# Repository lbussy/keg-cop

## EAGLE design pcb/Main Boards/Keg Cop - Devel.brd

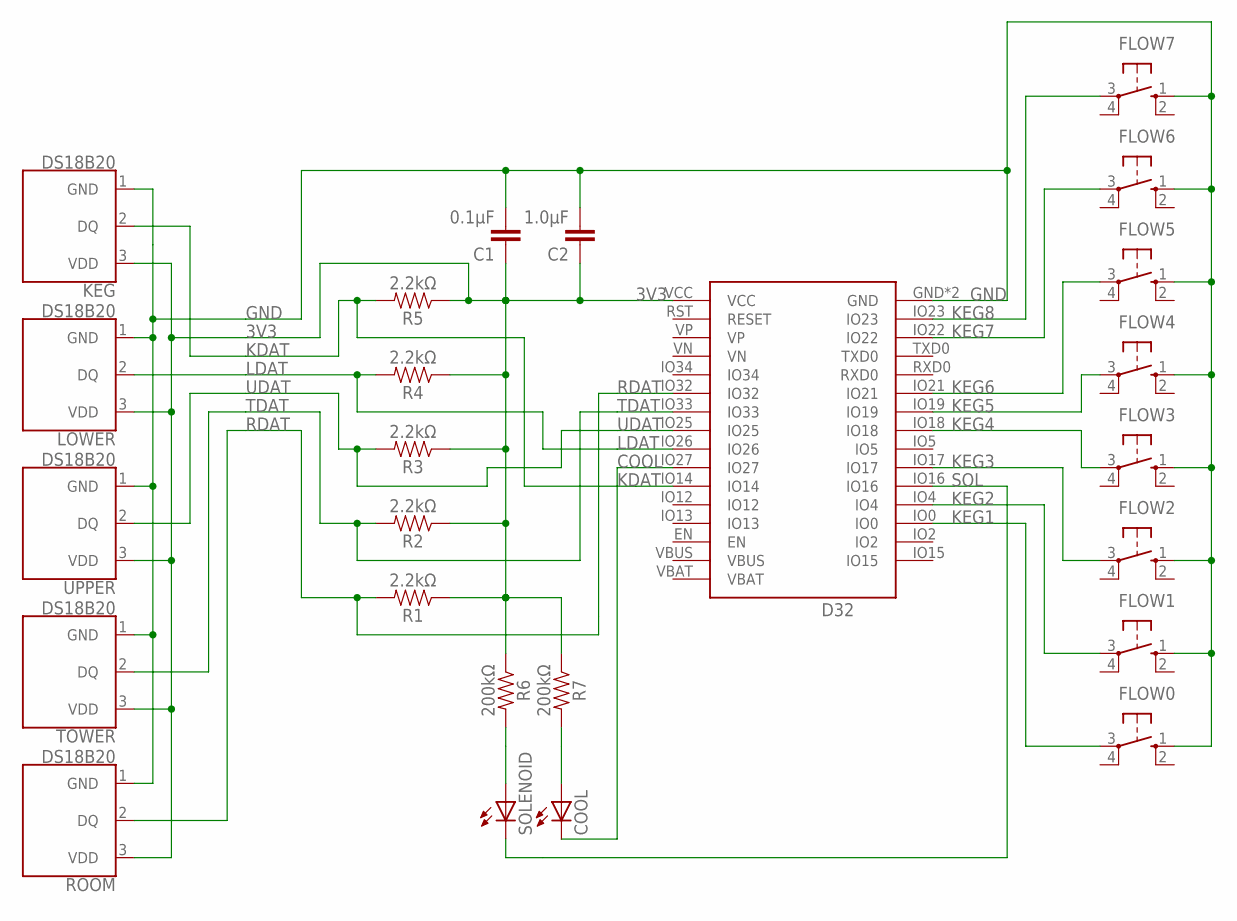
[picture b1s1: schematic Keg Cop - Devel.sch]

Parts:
C1: 0.1μF; CAP_PTH-2.54
C2: 1.0μF; CAP_PTH-2.54
COOL: LED3MM
D32: Lolin D32; D32_NO_BATT
FLOW0, FLOW1, FLOW2, FLOW3, FLOW4, FLOW5, FLOW6, FLOW7: 10-XX; B3F-10XX
KEG: DS18B20; TO-92-AMMO
LOWER: DS18B20; TO-92-AMMO
R1, R2, R3, R4, R5: 2.2kΩ; AXIAL-0.3
R6, R7: 200kΩ; AXIAL-0.3
ROOM: DS18B20; TO-92-AMMO
SOLENOID: LED3MM
TOWER: DS18B20; TO-92-AMMO
UPPER: DS18B20; TO-92-AMMO

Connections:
3V3: C1.1, C2.1, D32.VCC, KEG.3 (VDD), LOWER.3 (VDD), R1.P$1 (1), R2.P$1 (1), R3.P$1 (1), R4.P$1 (1), R5.P$1 (1), R6.P$1 (1), R7.P$1 (1), ROOM.3 (VDD), TOWER.3 (VDD), UPPER.3 (VDD)
COOL: COOL.K (C), D32.IO27
GND: C1.2, C2.2, D32.GND, D32.GND2 (GND), FLOW0.1 (S), FLOW1.1 (S), FLOW2.1 (S), FLOW3.1 (S), FLOW4.1 (S), FLOW5.1 (S), FLOW6.1 (S), FLOW7.1 (S), KEG.1 (GND), LOWER.1 (GND), ROOM.1 (GND), TOWER.1 (GND), UPPER.1 (GND)
KDAT: D32.IO14, KEG.2 (DQ), R5.P$2 (2)
KEG1: D32.IO0, FLOW0.3
KEG2: D32.IO4, FLOW1.3
KEG3: D32.IO17, FLOW2.3
KEG4: D32.IO18, FLOW3.3
KEG5: D32.IO19, FLOW4.3
KEG6: D32.IO21, FLOW5.3
KEG7: D32.IO22, FLOW6.3
KEG8: D32.IO23, FLOW7.3
LDAT: D32.IO26, LOWER.2 (DQ), R4.P$2 (2)
unnamed: COOL.A, R7.P$2 (2)
unnamed: R6.P$2 (2), SOLENOID.A
RDAT: D32.IO32, R1.P$2 (2), ROOM.2 (DQ)
SOL: D32.IO16, SOLENOID.K (C)
TDAT: D32.IO33, R2.P$2 (2), TOWER.2 (DQ)
UDAT: D32.IO25, R3.P$2 (2), UPPER.2 (DQ)

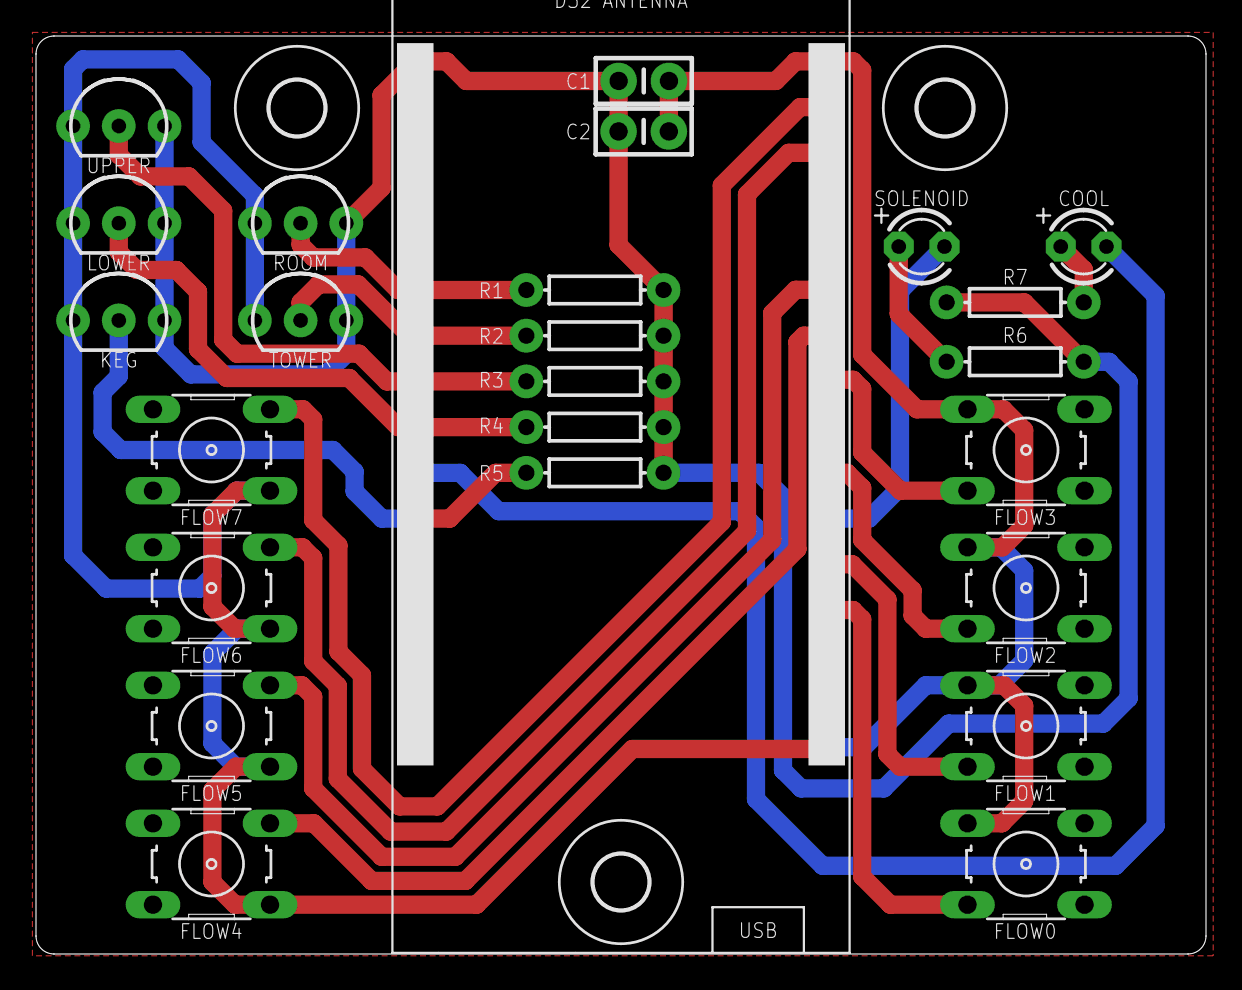
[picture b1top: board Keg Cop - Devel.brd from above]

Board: 2 copper layers, 65.0 x 51.0 mm, 28 parts (0 on the bottom side), 19 nets.

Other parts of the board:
U$1, U$2, U$3: 3,0

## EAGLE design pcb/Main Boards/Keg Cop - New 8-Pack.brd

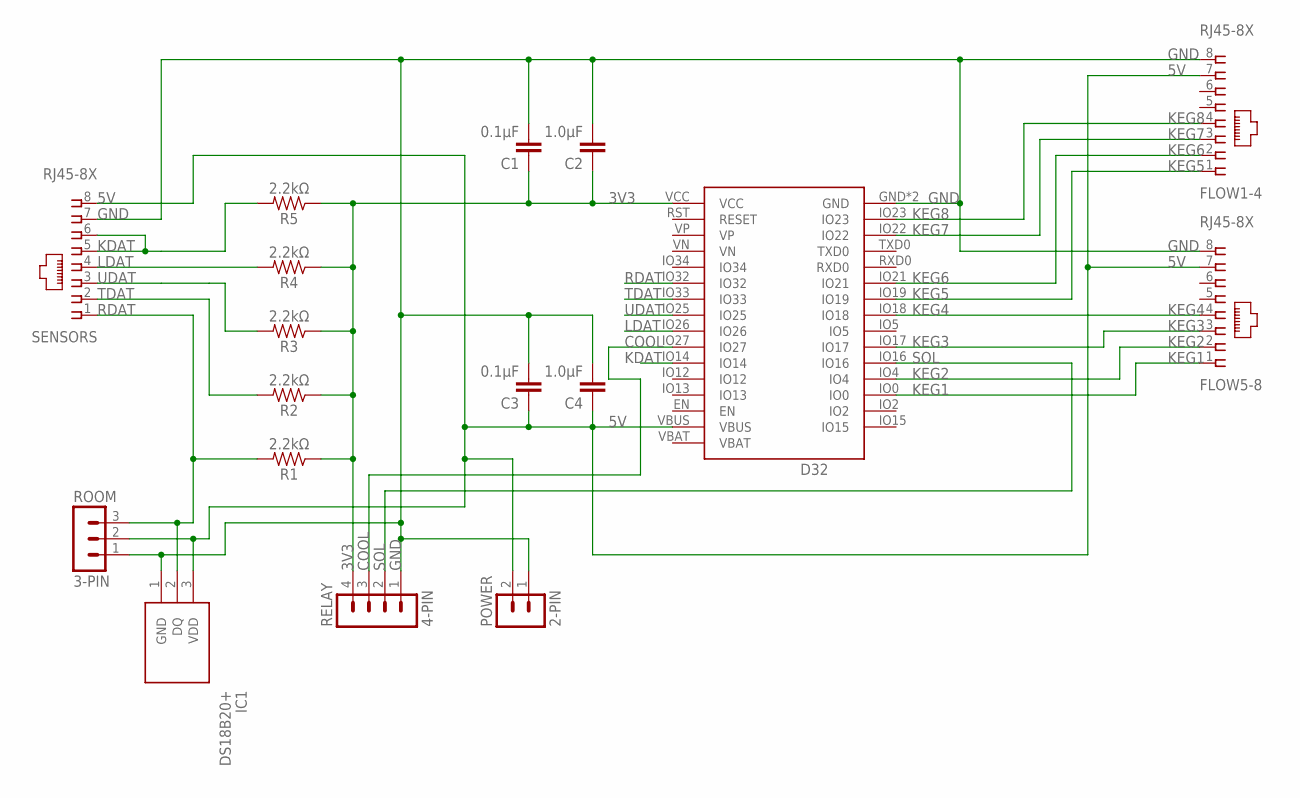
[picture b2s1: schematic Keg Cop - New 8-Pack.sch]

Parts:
C1, C3: 0.1μF; CAP_PTH-2.54
C2, C4: 1.0μF; CAP_PTH-2.54
D32: Lolin D32; D32_NO_BATT
FLOW1-4, FLOW5-8: RJ45-8X; RJ45-NO-SHIELD
IC1: DS18B20+; TO-92
POWER: 2-PIN; HDR-2_VERT
R1, R2, R3, R4, R5: 2.2kΩ; AXIAL-0.3
RELAY: 4-PIN; MA04-1
ROOM: 3-PIN; HDR-3_VERT
SENSORS: RJ45-8X; RJ45-NO-SHIELD

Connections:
3V3: C1.1, C2.1, D32.VCC, R1.P$1 (1), R2.P$1 (1), R3.P$1 (1), R4.P$1 (1), R5.P$1 (1), RELAY.4
5V: C3.1, C4.1, D32.VBUS, FLOW1-4.7, FLOW5-8.7, IC1.3 (VDD), POWER.2, ROOM.2, SENSORS.8
COOL: D32.IO27, RELAY.3
GND: C1.2, C2.2, C3.2, C4.2, D32.GND, D32.GND2 (GND), FLOW1-4.8, FLOW5-8.8, IC1.1 (GND), POWER.1, RELAY.1, ROOM.1, SENSORS.7
KDAT: D32.IO14, R5.P$2 (2), SENSORS.5, SENSORS.6
KEG1: D32.IO0, FLOW5-8.1
KEG2: D32.IO4, FLOW5-8.2
KEG3: D32.IO17, FLOW5-8.3
KEG4: D32.IO18, FLOW5-8.4
KEG5: D32.IO19, FLOW1-4.1
KEG6: D32.IO21, FLOW1-4.2
KEG7: D32.IO22, FLOW1-4.3
KEG8: D32.IO23, FLOW1-4.4
LDAT: D32.IO26, R4.P$2 (2), SENSORS.4
RDAT: D32.IO32, IC1.2 (DQ), R1.P$2 (2), ROOM.3, SENSORS.1
SOL: D32.IO16, RELAY.2
TDAT: D32.IO33, R2.P$2 (2), SENSORS.2
UDAT: D32.IO25, R3.P$2 (2), SENSORS.3

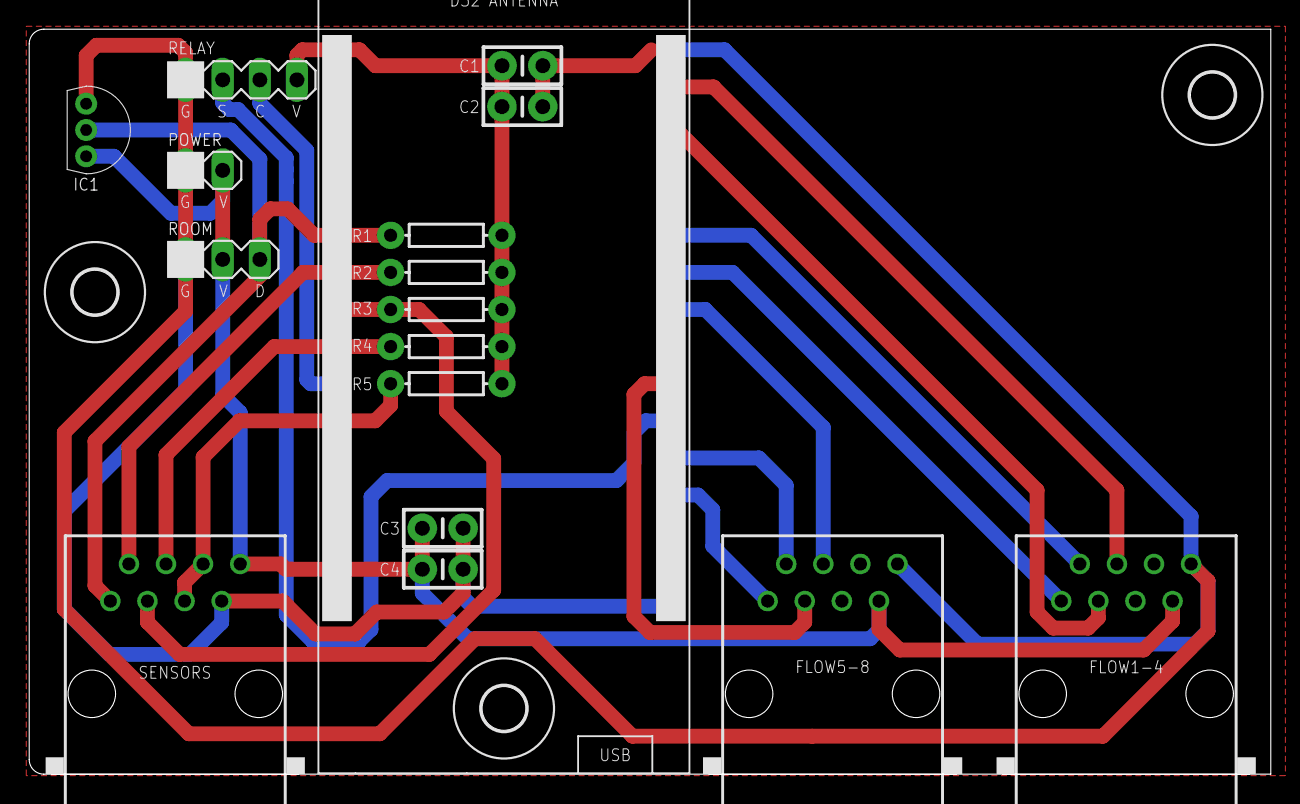
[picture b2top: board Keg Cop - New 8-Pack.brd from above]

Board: 2 copper layers, 85.0 x 51.0 mm, 20 parts (0 on the bottom side), 18 nets.

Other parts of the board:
U$1, U$2, U$3: 3,0

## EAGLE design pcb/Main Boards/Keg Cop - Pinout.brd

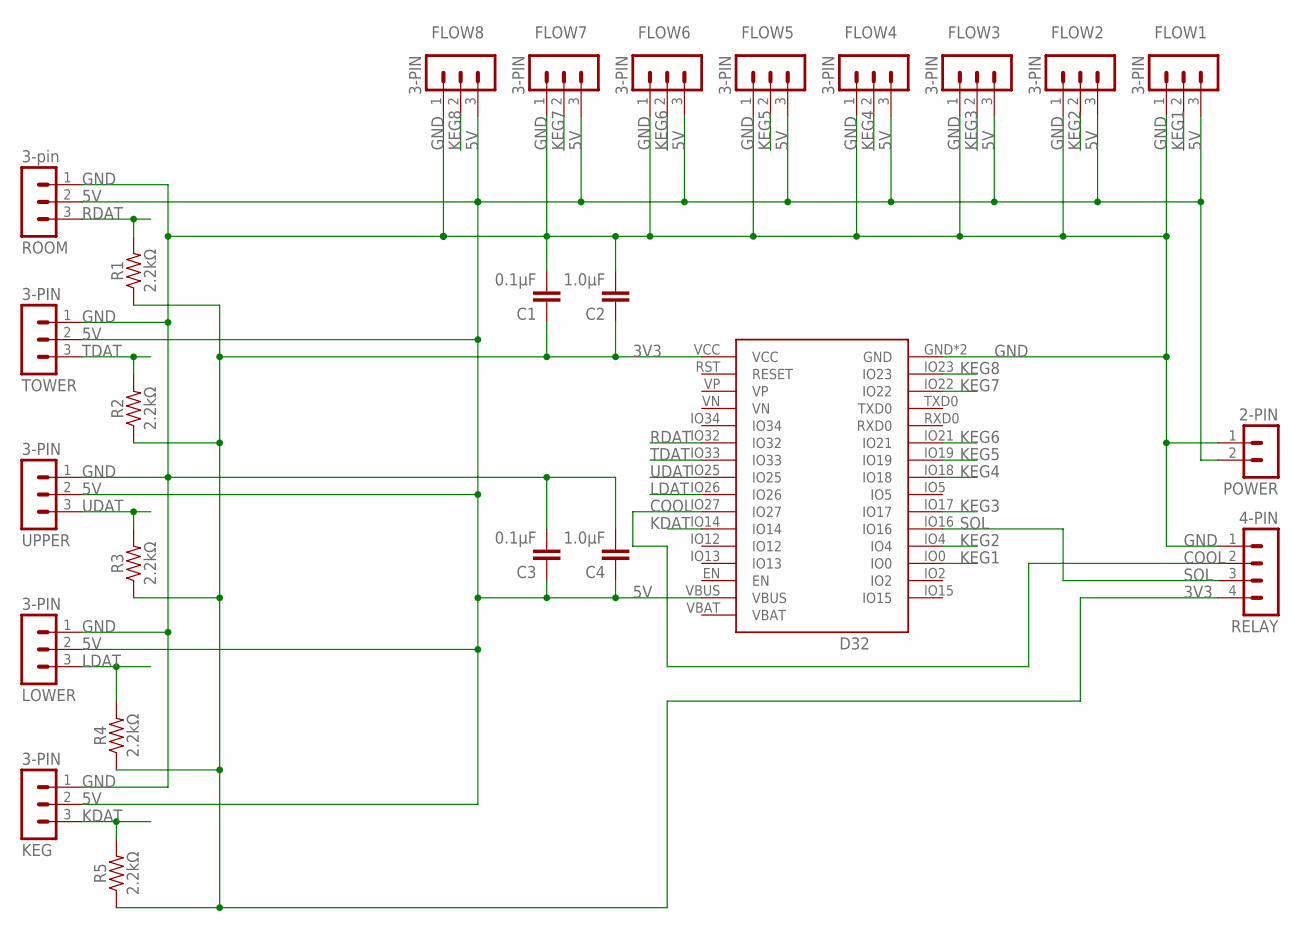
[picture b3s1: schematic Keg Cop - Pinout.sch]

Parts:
C1, C3: 0.1μF; CAP_PTH-2.54
C2, C4: 1.0μF; CAP_PTH-2.54
D32: U1; D32_NO_BATT
FLOW1, FLOW2, FLOW3, FLOW4, FLOW5, FLOW6, FLOW7, FLOW8: 3-PIN; MA03-1
KEG: 3-PIN; MA03-1
LOWER: 3-PIN; MA03-1
POWER: 2-PIN; HDR-2_VERT
R1, R2, R3, R4, R5: 2.2kΩ; AXIAL-0.3
RELAY: 4-PIN; MA04-1
ROOM: 3-pin; MA03-1
TOWER: 3-PIN; MA03-1
UPPER: 3-PIN; MA03-1

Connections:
3V3: C1.1, C2.1, D32.VCC, R1.P$1 (1), R2.P$1 (1), R3.P$1 (1), R4.P$1 (1), R5.P$1 (1), RELAY.4
5V: C3.1, C4.1, D32.VBUS, FLOW1.3, FLOW2.3, FLOW3.3, FLOW4.3, FLOW5.3, FLOW6.3, FLOW7.3, FLOW8.3, KEG.2, LOWER.2, POWER.2, ROOM.2, TOWER.2, UPPER.2
COOL: D32.IO27, RELAY.2
GND: C1.2, C2.2, C3.2, C4.2, D32.GND, D32.GND2 (GND), FLOW1.1, FLOW2.1, FLOW3.1, FLOW4.1, FLOW5.1, FLOW6.1, FLOW7.1, FLOW8.1, KEG.1, LOWER.1, POWER.1, RELAY.1, ROOM.1, TOWER.1, UPPER.1
KDAT: D32.IO14, KEG.3, R5.P$2 (2)
KEG1: D32.IO0, FLOW1.2
KEG2: D32.IO4, FLOW2.2
KEG3: D32.IO17, FLOW3.2
KEG4: D32.IO18, FLOW4.2
KEG5: D32.IO19, FLOW5.2
KEG6: D32.IO21, FLOW6.2
KEG7: D32.IO22, FLOW7.2
KEG8: D32.IO23, FLOW8.2
LDAT: D32.IO26, LOWER.3, R4.P$2 (2)
RDAT: D32.IO32, R1.P$2 (2), ROOM.3
SOL: D32.IO16, RELAY.3
TDAT: D32.IO33, R2.P$2 (2), TOWER.3
UDAT: D32.IO25, R3.P$2 (2), UPPER.3

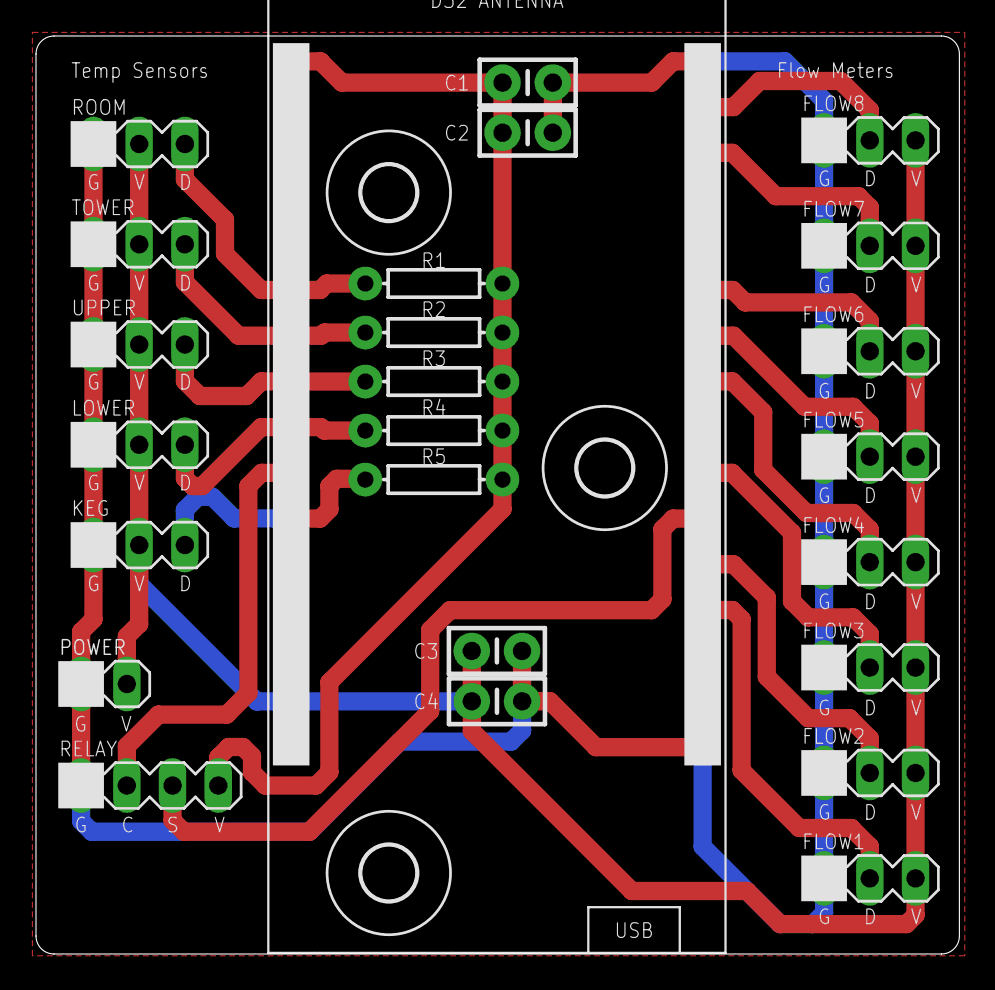
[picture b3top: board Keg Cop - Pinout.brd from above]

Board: 2 copper layers, 51.3 x 51.0 mm, 28 parts (0 on the bottom side), 18 nets.

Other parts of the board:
U$1, U$2, U$3: 3,0

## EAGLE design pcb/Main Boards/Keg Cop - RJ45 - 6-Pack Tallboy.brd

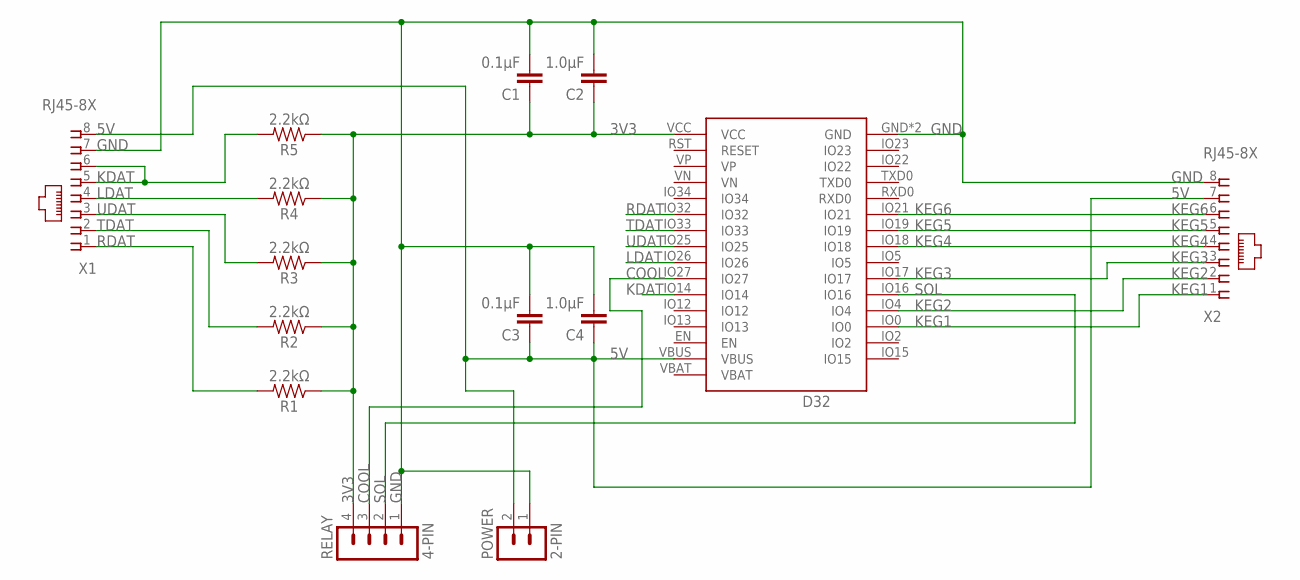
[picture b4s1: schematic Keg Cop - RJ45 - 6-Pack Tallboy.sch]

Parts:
C1, C3: 0.1μF; CAP_PTH-2.54
C2, C4: 1.0μF; CAP_PTH-2.54
D32: Lolin D32; D32_NO_BATT
POWER: 2-PIN; HDR-2_VERT
R1, R2, R3, R4, R5: 2.2kΩ; AXIAL-0.3
RELAY: 4-PIN; MA04-1
X1, X2: RJ45-8X; RJ45-NO-SHIELD

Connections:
3V3: C1.1, C2.1, D32.VCC, R1.P$1 (1), R2.P$1 (1), R3.P$1 (1), R4.P$1 (1), R5.P$1 (1), RELAY.4
5V: C3.1, C4.1, D32.VBUS, POWER.2, X1.8, X2.7
COOL: D32.IO27, RELAY.3
GND: C1.2, C2.2, C3.2, C4.2, D32.GND, D32.GND2 (GND), POWER.1, RELAY.1, X1.7, X2.8
KDAT: D32.IO14, R5.P$2 (2), X1.5, X1.6
KEG1: D32.IO0, X2.1
KEG2: D32.IO4, X2.2
KEG3: D32.IO17, X2.3
KEG4: D32.IO18, X2.4
KEG5: D32.IO19, X2.5
KEG6: D32.IO21, X2.6
LDAT: D32.IO26, R4.P$2 (2), X1.4
RDAT: D32.IO32, R1.P$2 (2), X1.1
SOL: D32.IO16, RELAY.2
TDAT: D32.IO33, R2.P$2 (2), X1.2
UDAT: D32.IO25, R3.P$2 (2), X1.3

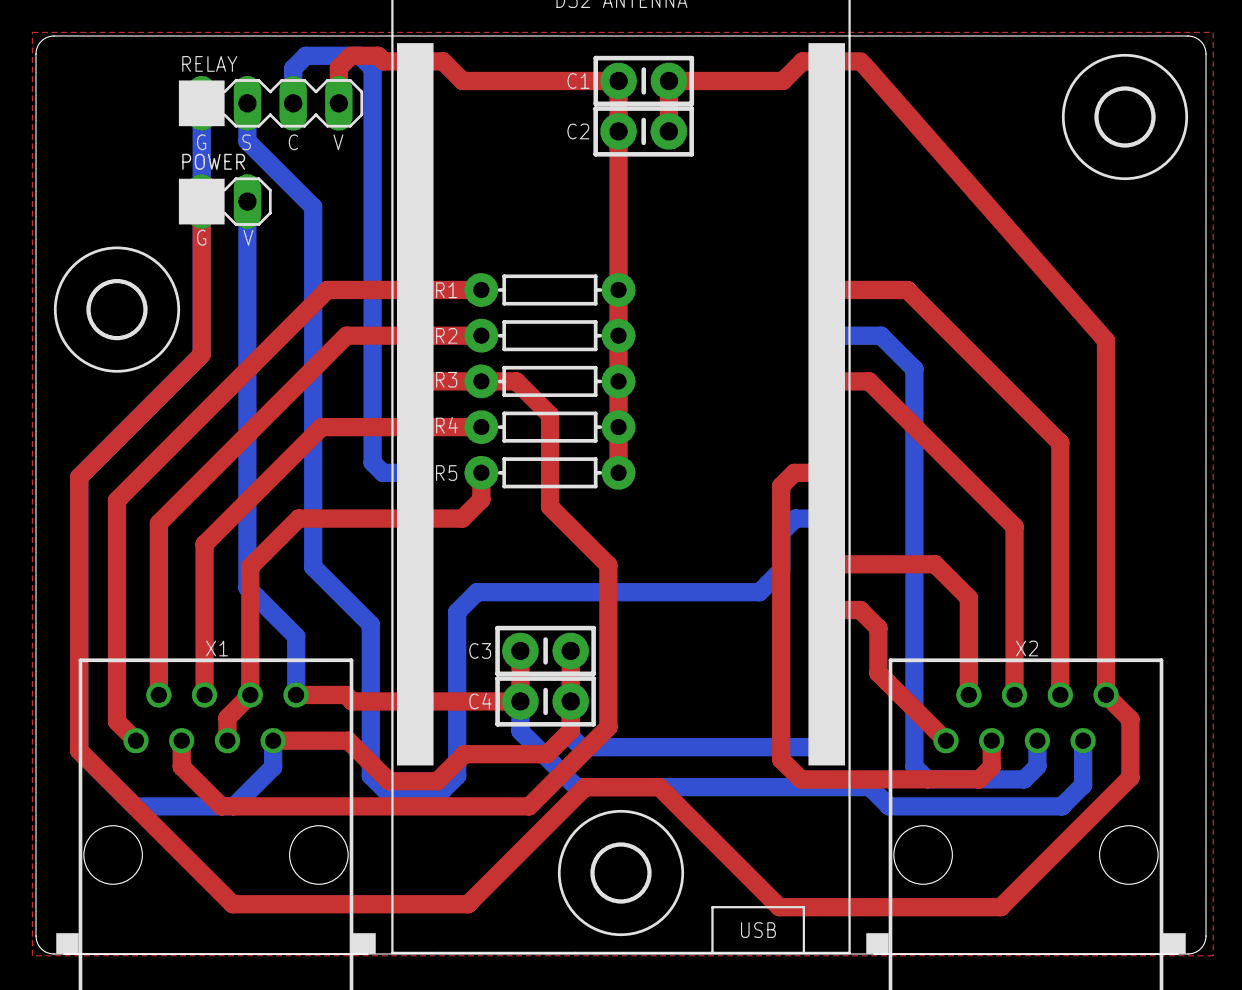
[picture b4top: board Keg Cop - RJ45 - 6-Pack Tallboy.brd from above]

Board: 2 copper layers, 65.0 x 51.0 mm, 17 parts (0 on the bottom side), 16 nets.

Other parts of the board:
U$1, U$2, U$3: 3,0

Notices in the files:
parts and their libraries:
SparkFun-Resistors: Licensing: Creative Commons ShareAlike 4.0 International - https://creativecommons.org/licenses/by-sa/4.0
